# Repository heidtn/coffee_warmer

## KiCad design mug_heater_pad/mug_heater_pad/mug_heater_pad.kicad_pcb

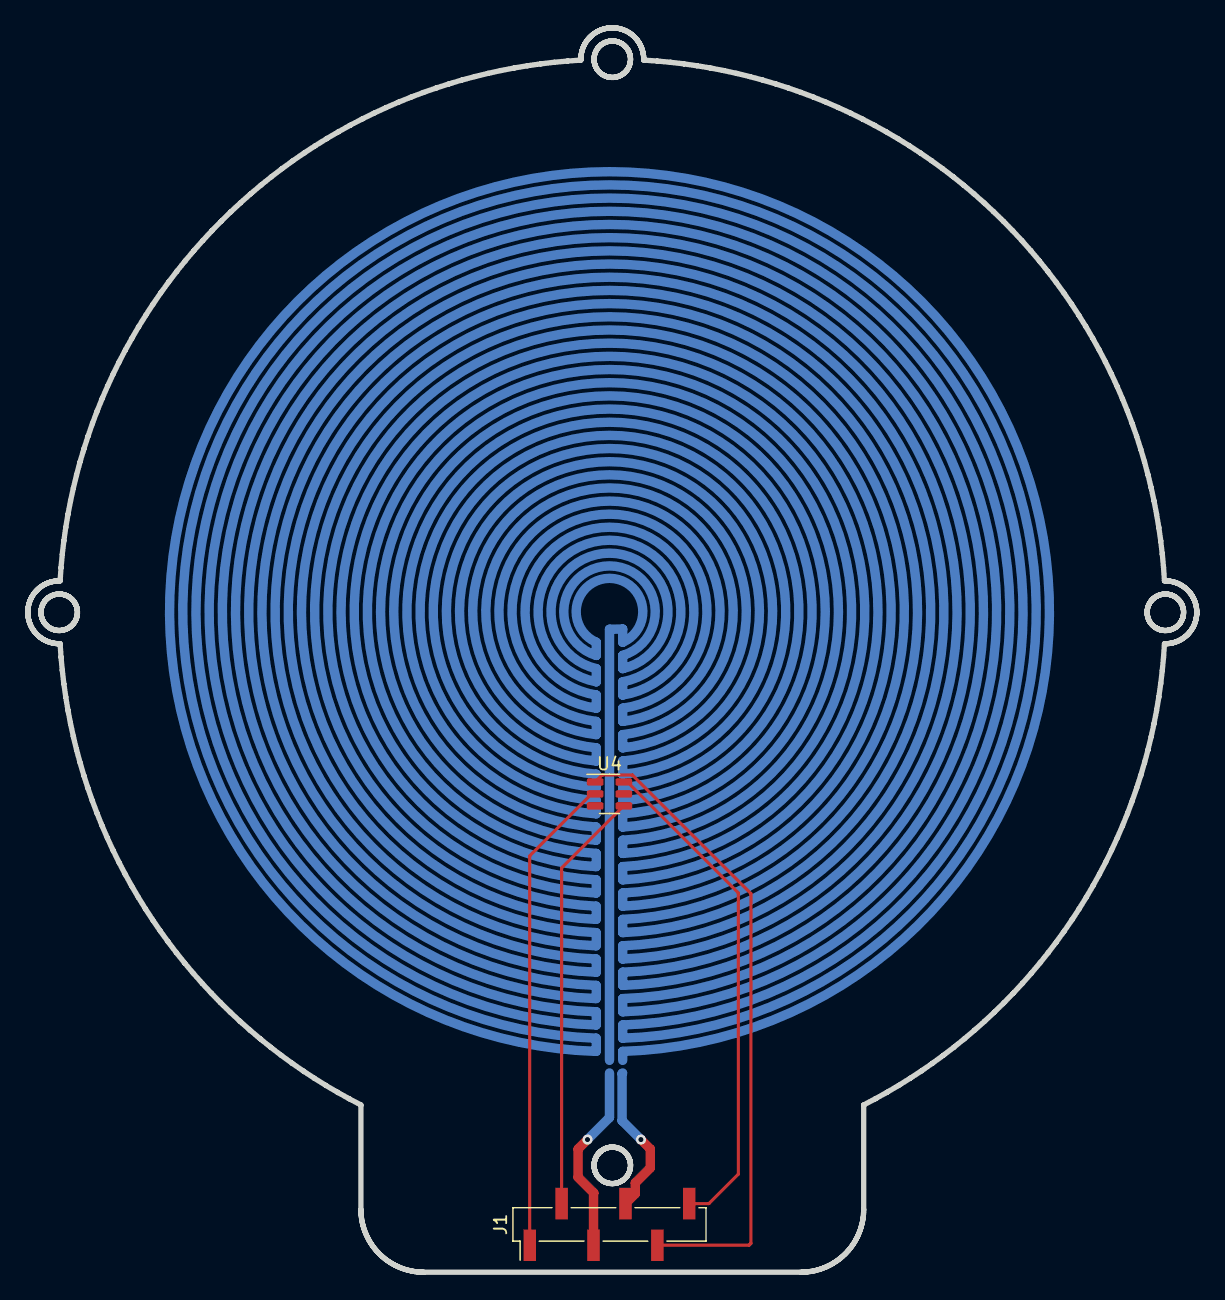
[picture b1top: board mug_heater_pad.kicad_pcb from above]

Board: 2 copper layers, 93.0 x 99.0 mm, 3 parts (1 on the bottom side), 6 nets.

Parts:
J1: Conn_01x06_Male; PinHeader_1x06_P2.54mm_Vertical_SMD_Pin1Left
R1: R; mug_heater_resistor_3737mm
U4: TMP101; SOT-23-6

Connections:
+3V3: J1.2, U4.4 (V+)
GND: J1.1, U4.2 (GND)
unnamed: J1.3, R1.1
unnamed: J1.4, R1.2
SCL: J1.5, U4.1 (SCL)
SDA: J1.6, U4.6 (SDA)

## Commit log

2023-01-09 initial version of heater pad design
